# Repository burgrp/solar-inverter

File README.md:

# solar-inverter

## Panel box

## Central box

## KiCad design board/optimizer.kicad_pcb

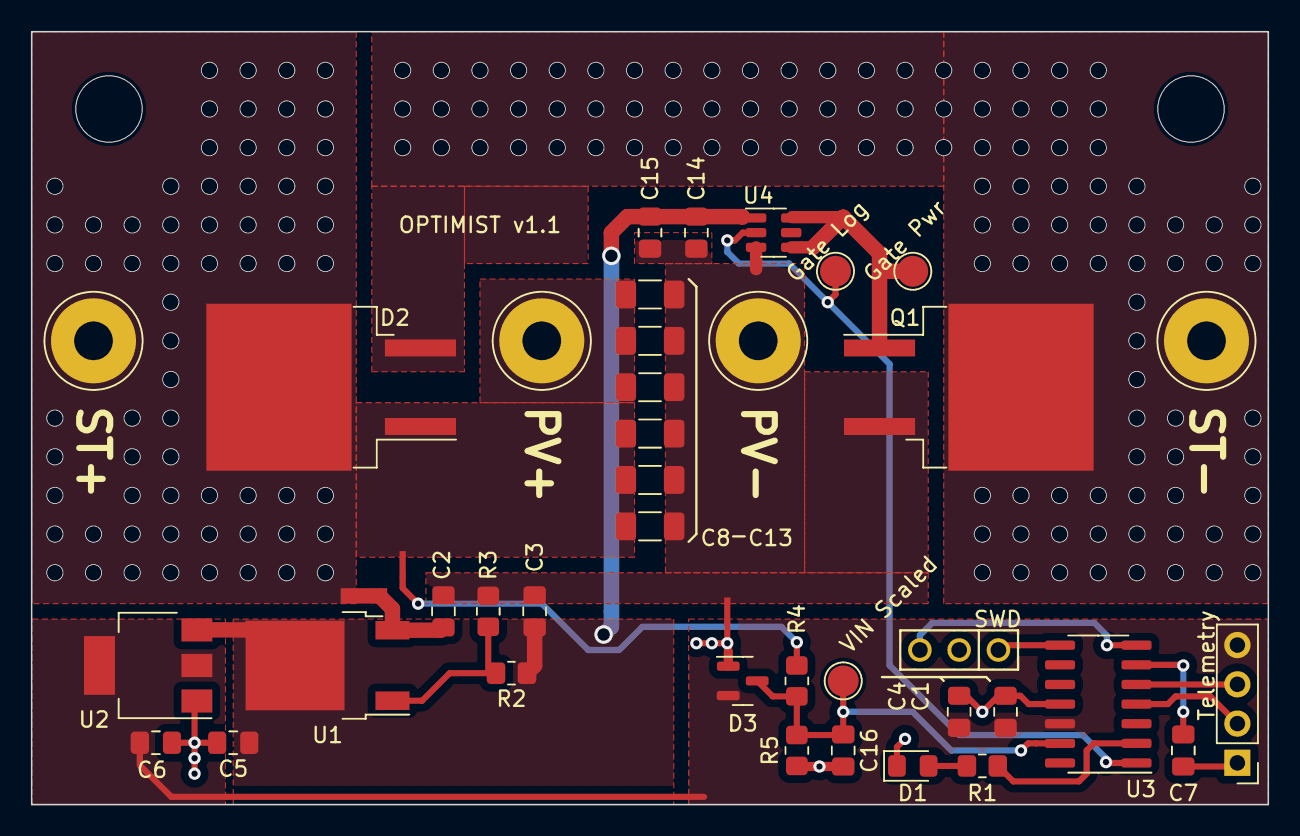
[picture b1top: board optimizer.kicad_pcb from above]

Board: 2 copper layers, 80.0 x 50.0 mm, 43 parts (0 on the bottom side), 19 nets.

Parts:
C1, C2, C7, C14, C16: 100n; C_0805_2012Metric_Pad1.18x1.45mm_HandSolder
C3, C4, C15: 1u; C_0805_2012Metric_Pad1.18x1.45mm_HandSolder
C5, C6: 10u; C_0805_2012Metric_Pad1.18x1.45mm_HandSolder
C8, C9, C10, C11, C12, C13: 10u/50V; C_1206_3216Metric_Pad1.33x1.80mm_HandSolder
D1: LED; LED_0805_2012Metric_Pad1.15x1.40mm_HandSolder
D2: DSS16-01AS; TO-263-2_TabPin1
D3: BAT54S; SOT-23
H1, H2: MountingHole; MountingHole_4.3mm_M4_ISO7380
J1: PV+; Wire 4mm2
J2: ST+; Wire 4mm2
J3: PV-; Wire 4mm2
J4: ST-; Wire 4mm2
J5: Telemetry; PinHeader_1x04_P2.54mm_Vertical
NT1: NetTie_2; NetTie 1 mm
NT2, NT3: NetTie_2; NetTie 0.4 mm
Q1: AOB2500L; TO-263-2
R1, R2, R5: 270R; R_0805_2012Metric_Pad1.20x1.40mm_HandSolder
R3: 2k26; R_0805_2012Metric_Pad1.20x1.40mm_HandSolder
R4: 10k; R_0805_2012Metric_Pad1.20x1.40mm_HandSolder
TP1: Gate Log; TestPoint_Pad_D2.0mm
TP2: Gate Pwr; TestPoint_Pad_D2.0mm
TP3: VIN Scaled; TestPoint_Pad_D2.0mm
U1: LM317_TO-252; TO-252-2
U2: AP1117-33; SOT-223-3_TabPin2
U3: ATSAMD09C13A-SS; SOIC-14_3.9x8.7mm_P1.27mm
U4: ZXGD3009E6; SOT-23-6
X1: SWD

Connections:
+3V3: C1.1, C4.1, C6.1, D3.2, J5.4, U2.2 (VO), U3.12 (VDD)
+12V: C3.1, C5.1, C14.1, C15.1, R2.1, U1.2 (VO), U2.3 (VI), U4.1 (VCC)
/GATE_LOG: TP1.1, U3.1 (PA05), U4.2 (IN)
/GATE_PWR: Q1.1 (G), TP2.1, U4.4 (SINK), U4.6 (SOURCE)
/LED: R1.1, U3.2 (PA08/XIN)
/PWR_GND: C2.2, C3.2, C8.1, C9.1, C10.1, C11.1, C12.1, C13.1, C14.2, C15.2, J3.1, NT3.2, Q1.3 (S), R3.2, U4.3 (VEE)
/PWR_GND_OUT: D2.2 (A), J4.1, Q1.2 (D)
/PWR_P: C8.2, C9.2, C10.2, C11.2, C12.2, C13.2, D2.1 (K), J1.1, J2.1, NT1.1, NT2.1
/SWITCH_PATH1: C2.1, NT1.2, U1.3 (VI)
/TELEMETRY_1: J5.2, U3.4 (PA14)
/TELEMETRY_2: J5.3, U3.5 (PA15)
/V_FULL: NT2.2, R4.1
/V_SCALE: C16.1, D3.3, R4.2, R5.1, TP3.1, U3.13 (PA02)
GND: C1.2, C4.2, C5.2, C6.2, C7.1, C16.2, D1.1 (K), D3.1, J5.1, NT3.1, R5.2, U2.1 (GND), U3.11 (GND), X1.2 (GND)
unnamed: D1.2 (A), R1.2
unnamed: R2.2, R3.1, U1.1 (ADJ)
unnamed: C7.2, U3.6 (PA28/~RST)
unnamed: U3.7 (PA30/SWCLK), X1.3 (SWCLK)
unnamed: U3.8 (PA31/SWDIO), X1.1 (SWDIO)
